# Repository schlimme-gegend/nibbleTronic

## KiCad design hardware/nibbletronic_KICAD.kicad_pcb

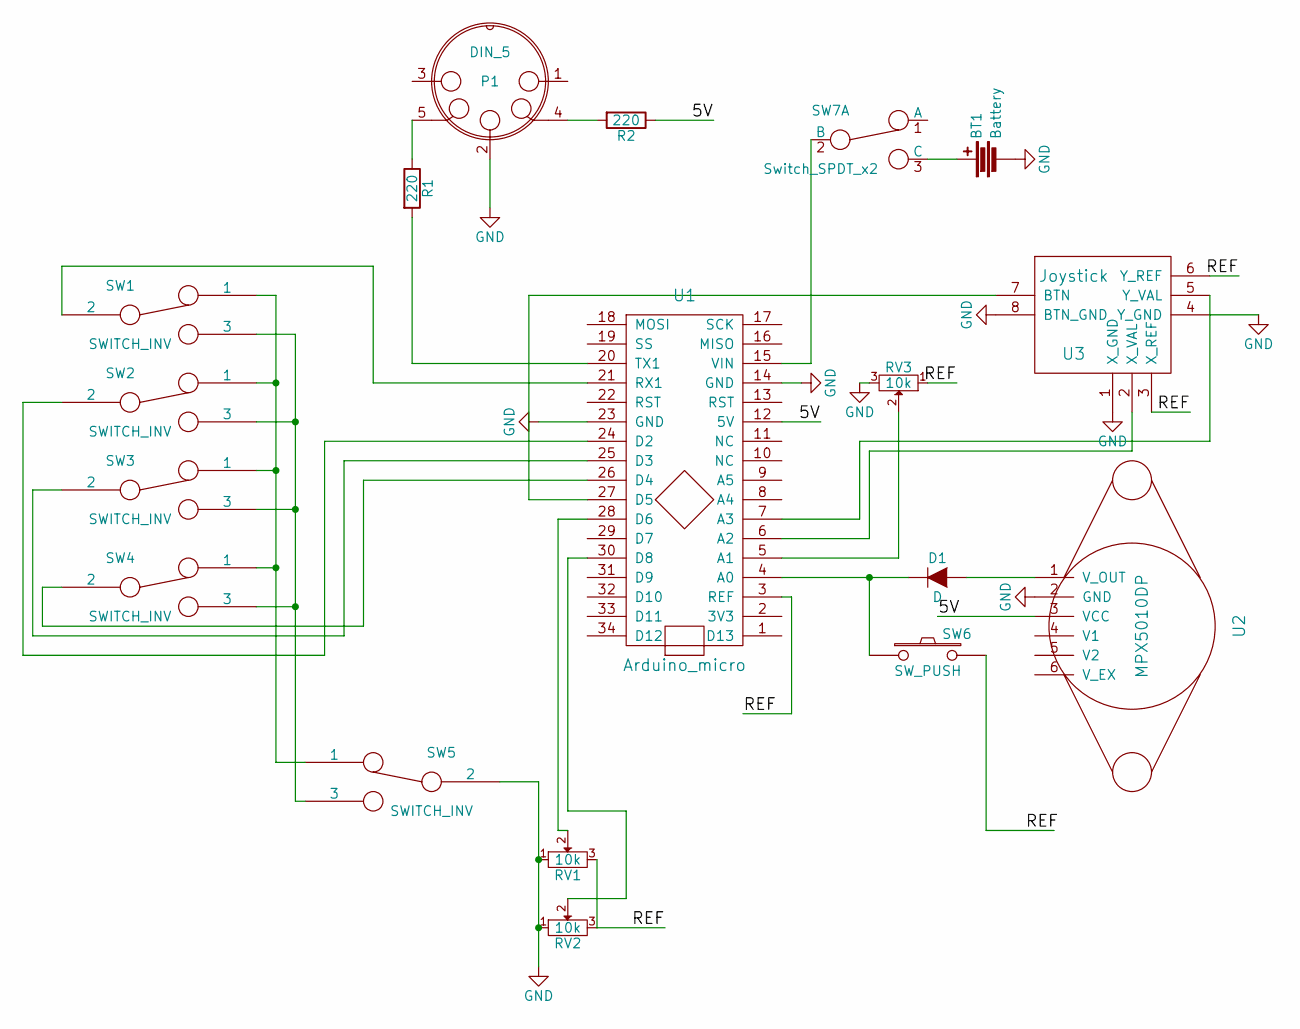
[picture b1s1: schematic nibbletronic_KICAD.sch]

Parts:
BT1: Battery; 9V_BATTERY_CLIP
D1: D; D_0805
P1: DIN_5; HIRSCHMANN_MAB_5
R1, R2: 220; R_0805_HandSoldering
RV1, RV2, RV3: 10k; ALPS_402125
SW1, SW2, SW3, SW4: SWITCH_INV; MARQUARDT_SPDT
SW5: SWITCH_INV; ESP40XX
SW6: SW_PUSH; SMD_Pushbutton
SW7: Switch_SPDT_x2; ESP40XX
U1: Arduino_micro; ARDU_MICRO_SOCKET
U2: MPX5010DP
U3: Joystick; ALPS_RKJXP

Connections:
/5V: R2.1, U1.12 (5V), U2.3 (VCC)
/REF: RV1.3, RV2.3, RV3.1, SW6.2, U1.3 (REF), U3.3 (X_REF), U3.6 (Y_REF)
GND: BT1.2, P1.2, RV1.1, RV2.1, RV3.3, SW5.2, U1.14 (GND), U1.23 (GND), U2.2 (GND), U3.1 (X_GND), U3.4 (Y_GND), U3.8 (BTN_GND)
unnamed: BT1.1, SW7.3 (C)
unnamed: D1.1 (K), SW6.1, U1.4 (A0)
unnamed: D1.2 (A), U2.1 (V_OUT)
unnamed: P1.4, R2.2
unnamed: P1.5, R1.1
unnamed: R1.2, U1.20 (TX1)
unnamed: RV1.2, U1.28 (D6)
unnamed: RV2.2, U1.30 (D8)
unnamed: RV3.2, U1.5 (A1)
unnamed: SW1.1, SW2.1, SW3.1, SW4.1, SW5.1
unnamed: SW1.2, U1.21 (RX1)
unnamed: SW1.3, SW2.3, SW3.3, SW4.3, SW5.3
unnamed: SW2.2, U1.24 (D2)
unnamed: SW3.2, U1.25 (D3)
unnamed: SW4.2, U1.26 (D4)
unnamed: SW7.2 (B), U1.15 (VIN)
unnamed: U1.6 (A2), U3.2 (X_VAL)
unnamed: U1.7 (A3), U3.5 (Y_VAL)
unnamed: U1.27 (D5), U3.7 (BTN)

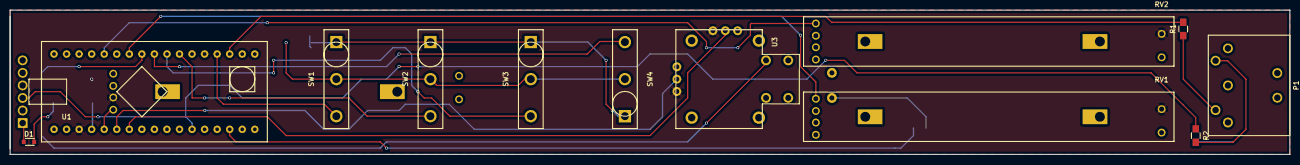
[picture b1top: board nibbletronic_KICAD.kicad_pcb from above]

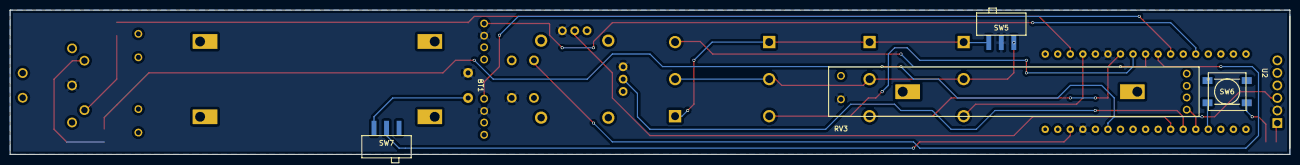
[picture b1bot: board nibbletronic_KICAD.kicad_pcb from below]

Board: 2 copper layers, 259.1 x 29.2 mm, 18 parts (6 on the bottom side), 22 nets.

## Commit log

2014-09-16 finally doing this
2014-09-16 renamed source file to conform with ardu ide standard
2014-09-16 removed waiting timer from transmitting pressure changes.
2014-09-18 fixed midi bullshit: loade old firmware that talked expected a button on pin 1 wher now the MIDI interface is.
2014-10-02 Switched to 4 bit notes plus 2 octavebits.
2015-12-28 cleaned up definitions.
2016-01-01 Reoragnized folders, added schematics
2016-01-02 added .gitignore with definitions to filter .bak and .bck files created byKiCAD
2016-01-02 renamed parts library
2016-07-11 Added components, created PCB
2016-07-11 Added footprint library
2016-10-09 Changed footprints for slider, joystick and mode selector switch, added diode and power switch
2016-10-09 Changed octave code to accept slider input
2016-10-09 merged local copy with hosted repository
2016-10-09 Changed PCBlayout, added new footprints, changed spacing, switched to SMD diode, resistors, buttons and switches.
2016-10-11 Changed switches and button due to parts availability, updated BOM
2016-12-01 Beginning overhaul of firmware to work with 1.0alpha hardware.
2016-12-07 Introducing the pressureControlledMIDI class
2016-12-14 Sending one pyte too many,looking into it.
2017-01-18 Post 33c3 update
2017-01-23 included MIDI.h (https://github.com/FortySevenEffects/arduino_midi_library/), hit a brick wall.
2017-01-25 fixed note interpretation
2017-01-25 Added slider class, cleanup
2017-01-25 Added added baseOctave, further cleanup
2017-01-25 Moved pressureControlledMidi.send to update method, added comments.
2017-01-25 Added Joystick Y axis, implemented Witzmans mystery fix
2017-01-27 Joytester
2017-01-29 Added Noise rediction for Sliders
    My joystick controller kind of flooded the output with 1 value changes when not moved. So i integrated a noise reduction.
2017-01-30 Removed output noise
    - added noise reduction into slider class for joystick
    - lowered octave range Slider (constantly changed beween 73 & 83 in highest octve
2017-02-09 Create RotEncEEPROM
2017-02-09 Update RotEncEEPROM
2017-02-09 EEPORN UPDATE 1
    -Added EEPROM READ for CC Values
    -Temporary global EEPROM Write
    -Prepared Pin Settings for Board V2 (Changing pins for note Switches & rotary Encoder
    - Fixed Slider joyX/X() , Slider left/rightSlider() & pressureControlledMIDI volume/detune() to be in main loop - needed for assigning EEPROM Values
2017-02-09 Revert "Witzman rot enc eeprom"
2017-02-09 Changed detune tolerance to prevent midi spamming
2017-02-10 ENCODER UPDATE
    - Added Rotary Encoder (Pin 10, 11 & 12)
    - Send Encoder value on CC 192 for Midi program change
2017-02-11 Slider Update
    - Changed slider inputs based on hardware hotfix described here: https://github.com/schlimme-gegend/nibbleTronic/issues/12
    - Activated sliders in Code
    All hardware working now
2017-02-19 Beginning Hardware Revision 2.0
2017-02-20 v 2.0 Schematic
    Added touch sensor and rotenc to schematic, removed buttons and octave
    slider, added break outs for unused pins and i2c
2017-02-23 Hardware 2.0: Touch Buttons and a RotEnc
    - Microswitches are replaced by touch sensors with a dedicated IC
    - Octave slider has been replaced by two touch sensors
    - Added a Rotenc at pins D10-12 and D9 for the Button.
    - I2C and all remaining pins (A1, D4, D5, D8, D13), as well as GND, Ref,
    3.3/5V have been broken out for easier access
2017-03-05 2nd Encoder + TM1637Display
    - added 2nd rotary encoder
    - added TM1637Display (4 Digits - 7 Segments)
    - Currenty due to pin restriction shares pin 12 with Display and first encoder
